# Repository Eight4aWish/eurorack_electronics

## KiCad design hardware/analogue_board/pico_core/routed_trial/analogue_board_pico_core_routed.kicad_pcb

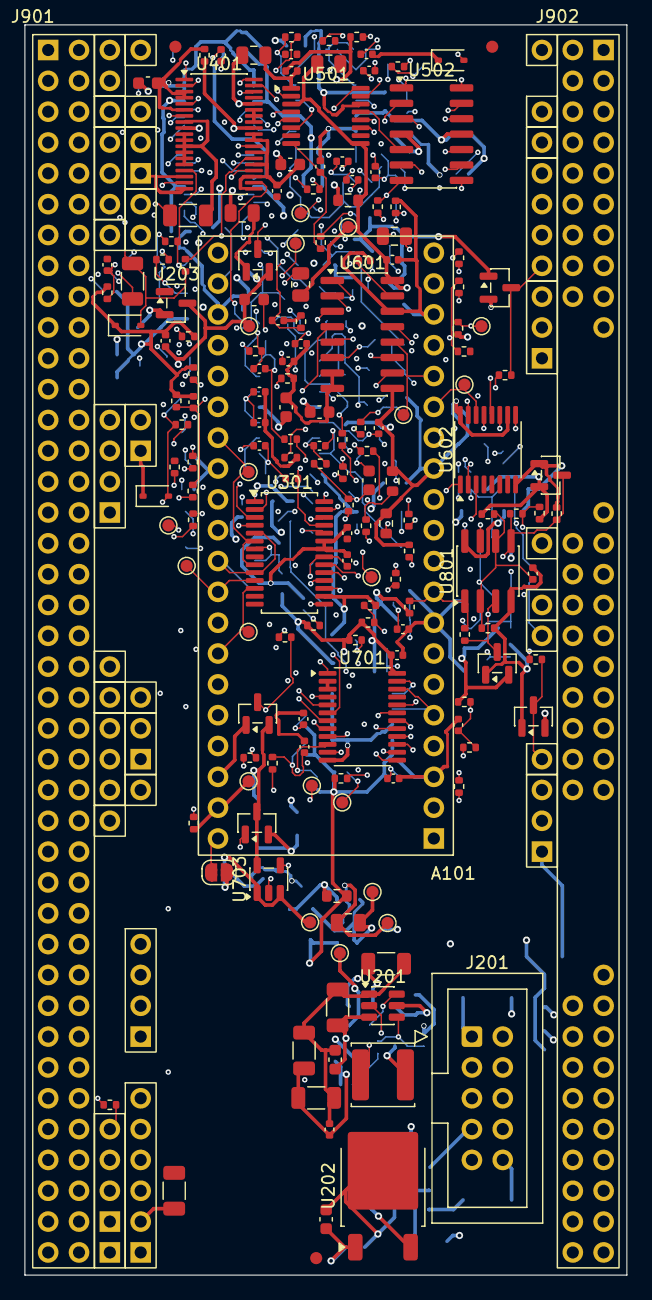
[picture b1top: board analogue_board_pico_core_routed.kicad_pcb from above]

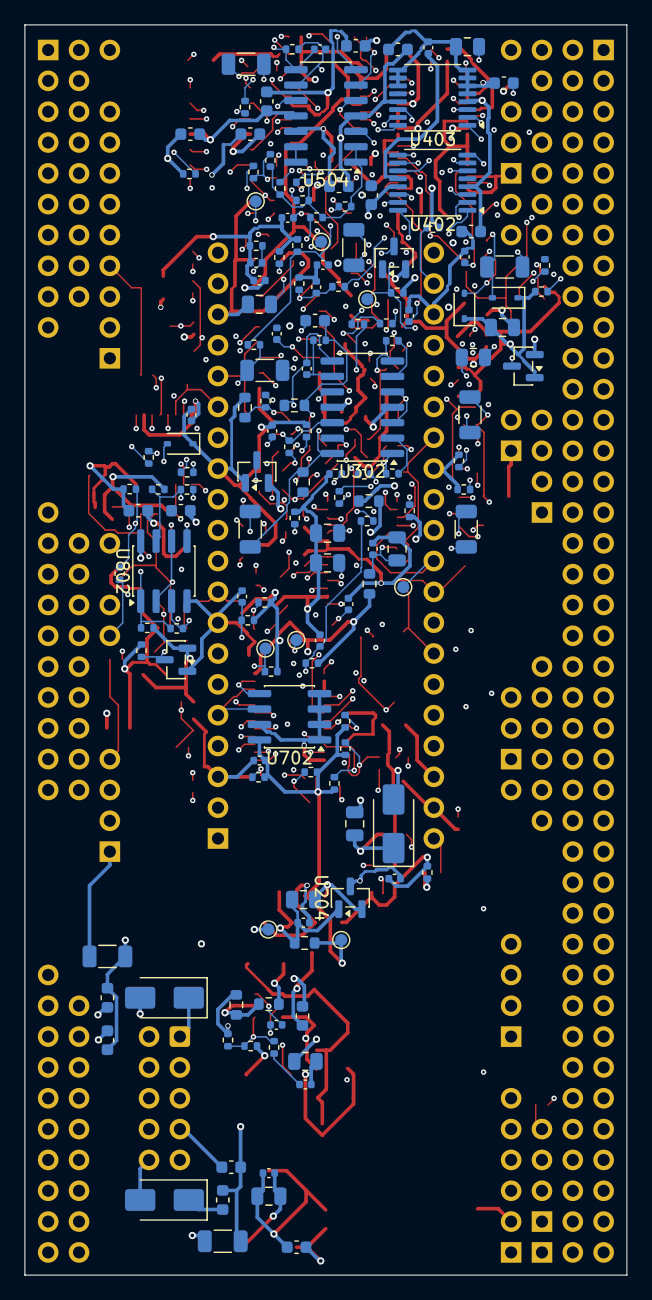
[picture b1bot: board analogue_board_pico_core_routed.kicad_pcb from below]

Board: 6 copper layers, 49.6 x 103.0 mm, 354 parts (152 on the bottom side), 252 nets.

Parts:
A101: Raspberry Pi Pico 2; Pico2_Socket
C201, C203, C205, C206: 10u 50V; C_1206_3216Metric
C202, C204, C207, C215, C319, C320, C415, C416, C418, C419, C511, C512, C513, C514, C801, C802: 100n 50V; C_0603_1608Metric
C208, C212, C217, C302, C304, C306, C309, C312, C405, C417, C420, C502, C602, C604, C605, C606, C607, C608, C609, C610, C611, C701, C702, C703, C704, C705, C710, C711, C712, C803: 100n 16V; C_0402_1005Metric
C209: 470p 50V; C_0402_1005Metric
C210, C211, C407: 22u 25V; C_1206_3216Metric
C213, C216, C219, C221, C222, C301, C303, C305, C403, C404, C408, C501, C603: 10u 25V; C_0805_2012Metric
C214, C401, C402, C406: 1u 50V; C_0603_1608Metric
C218, C220, C503, C601: 1u 25V; C_0402_1005Metric
C307, C310, C313, C314, C316, C317, C505, C506, C507, C508, C509, C510: 100p 50V; C_0402_1005Metric
C308, C311: 1u 50V; C_0805_2012Metric
C315, C318: 1n C0G 50V; C_0603_1608Metric
C409, C410, C411, C412, C413, C414, C504: 1n 50V; C_0402_1005Metric
C706, C707, C708, C709: 10n 50V; C_0402_1005Metric
C713: 47u 10V; C_1206_3216Metric
D201, D202, D203: SS34; D_SMA
D301, D302, D801, D802, D803, D804: BAT54S; SOT-23
D401, D402, D403, D404, D405, D406: PESD15VL1BA; D_SOD-323
D601, D602, D603, D604: BAV99; SOT-23
FB201, FB202, FB203, FB301: BLM18PG121; L_0603_1608Metric
FID901, FID902, FID903: Fiducial; Fiducial_1mm_Mask2mm
J101: Spare GPIO, RUN; WiringHoles_1x04_G4
J201: Eurorack power 2x5 shrouded; IDC-Header_2x05_P2.54mm_Vertical
J303: Codec RST; WiringHoles_1x02_G2
J310, J412, J710, J810: Holes, left top; WiringHoles_1x01
J311, J411, J711, J713, J811: Holes, left bottom; WiringHoles_1x01
J312, J413, J812: Holes, right top; WiringHoles_1x01
J313, J414, J615, J813: Holes, right middle; WiringHoles_1x01
J410, J712: Holes, left top; WiringHoles_1x02
J603: Gate expansion: QH', SRCLK, RCLK, OE; WiringHoles_1x06_G6
J610: Holes, left top; WiringHoles_1x03
J611: Holes, left bottom; WiringHoles_1x03
J612: Holes, left top; WiringHoles_1x02_G2
J613: Holes, left bottom; WiringHoles_1x02_G2
J614: Holes, right top; WiringHoles_1x04
J703: I2C holes for a wired display; WiringHoles_1x04_G4
J704: WS2812 chain holes; WiringHoles_1x05_G4_5
J714: Holes, right top; WiringHoles_1x03_G3
J715: Holes, right middle; WiringHoles_1x03_G3
J901: Edge strip, left; EdgeStrip_40_Left
J902: Edge strip, right; EdgeStrip_40_Right
JP201: ESP32-P4: bridge; SolderJumper-2_P1.3mm_Open_RoundedPad1.0x1.5mm
L201: 15uH; L_Sunlord_SWPA5040S
Q201: AO3401A; SOT-23
R201: 510k; R_0603_1608Metric
R202: 75k; R_0603_1608Metric
R203, R307, R311: 15k; R_0402_1005Metric
R204, R205: 2k; R_0402_1005Metric
R206: 0R; R_0805_2012Metric
R207, R208, R209: 0R; R_0603_1608Metric
R210: 680R; R_0603_1608Metric
R211, R309, R313, R604, R606, R608, R610, R612, R614: 1M; R_0402_1005Metric
R212, R308, R312, R405, R409, R413, R417, R421, R425, R802, R803, R806, R807, R810, R811, R814, R815: 100k; R_0402_1005Metric
R301, R302, R303, R401, R402, R403, R501, R504, R506, R508, R510, R512, R514, R602, R615, R616, R701, R703, R705, R707, R709, R711, R713, R715, R717, R719, R801, R804, R805, R808, R809, R812, R813, R816, R817, R818: 10k; R_0402_1005Metric
R304: 5.1R; R_0603_1608Metric
R305, R310, R314, R317, R318, R324, R325, R404, R408, R412, R416, R420, R424, R603, R605, R607, R609, R611, R613, R617, R618, R619, R620, R702, R704, R706, R708, R710, R712, R714, R716, R718: 1k; R_0402_1005Metric
R306: 220k; R_0603_1608Metric
R315, R316, R322, R323, R502: 12k; R_0402_1005Metric
R319, R320, R326, R327: 30k; R_0603_1608Metric
R321, R328, R406, R410, R414, R418, R422, R426: 1k; R_1206_3216Metric
R407, R411, R415, R419, R423, R427: 4.7k; R_0402_1005Metric
R503: 22k; R_0402_1005Metric
R505, R507, R509, R511, R513, R515: 33k; R_0402_1005Metric
R601: 100R; R_0805_2012Metric
R720, R721: 2.2k; R_0402_1005Metric
R722: 330R; R_0402_1005Metric
TP201: +12V; TestPoint_Pad_D1.0mm
TP202: -12V; TestPoint_Pad_D1.0mm
TP203, TP204: GND; TestPoint_Pad_D1.0mm
TP205: +5VD; TestPoint_Pad_D1.0mm
TP206: +5VA; TestPoint_Pad_D1.0mm
TP207: +3V3A; TestPoint_Pad_D1.0mm
TP208: +3V3D; TestPoint_Pad_D1.0mm
TP209: MOD_5V; TestPoint_Pad_D1.0mm
TP301: MCLK; TestPoint_Pad_D1.0mm
TP302: BCK; TestPoint_Pad_D1.0mm
TP303: LRCK; TestPoint_Pad_D1.0mm
TP304: I2S_DOUT; TestPoint_Pad_D1.0mm
TP305: I2S_DIN; TestPoint_Pad_D1.0mm
TP401: SPIA_SCK; TestPoint_Pad_D1.0mm
TP402: SPIA_MOSI; TestPoint_Pad_D1.0mm
TP403: SPIA_MISO; TestPoint_Pad_D1.0mm
TP404: CS_ADC; TestPoint_Pad_D1.0mm
TP405: CS_DAC; TestPoint_Pad_D1.0mm
TP601: SPIB_SCK; TestPoint_Pad_D1.0mm
TP602: SPIB_MOSI; TestPoint_Pad_D1.0mm
TP603: SPIB_MISO; TestPoint_Pad_D1.0mm
TP604: CS_595; TestPoint_Pad_D1.0mm
TP605: CS_POT; TestPoint_Pad_D1.0mm
TP701: SDA; TestPoint_Pad_D1.0mm
TP702: SCL; TestPoint_Pad_D1.0mm
TP703: EXP_INT; TestPoint_Pad_D1.0mm
U201: TPS54308DDCR; SOT-23-6
U202: L78M05ABDT-TR; TO-252-2_PasteShapes
U203, U204: XC6206P332MR-G; SOT-23
U301: PCM3060PWR; TSSOP-28_4.4x9.7mm_P0.65mm
U302, U502, U504: TL074HIDR; SOIC-14_3.9x8.7mm_P1.27mm
U401: ADS8688IDBTR; TSSOP-38_4.4x9.7mm_P0.5mm
U402, U403: DG412DQ-T1-E3; TSSOP-16_4.4x5mm_P0.65mm
U501: DAC8568IAPWR; TSSOP-16_4.4x5mm_P0.65mm
U601: MCP3208-CI/SL; SOIC-16_3.9x9.9mm_P1.27mm
U602: 74HCT595PW; TSSOP-16_4.4x5mm_P0.65mm
U701: TCA9555PWR; TSSOP-24_4.4x7.8mm_P0.65mm
U702: M24C64-RMN6TP; SOIC-8_3.9x4.9mm_P1.27mm
U703: SN74AHCT1G125DBVR; SOT-23-5
U801, U802: LM393DR2G; SOIC-8_3.9x4.9mm_P1.27mm

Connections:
+3V3A: C501.1, C502.1, C601.1, C602.1, R208.2, R601.1, TP207.1, U501.3, U501.9, U601.16
+3V3D: C404.1, C405.1, C701.1, C711.1, D801.2, D802.2, D803.2, D804.2, J703.3, R209.2, R210.1, R304.1, R305.1, R401.1, R402.1, R501.1, R602.1, R615.1, R616.1, R701.1, R703.1, R705.1, R707.1, R709.1, R711.1, R713.1, R715.1, R717.1, R719.1, R720.1, R721.1, R804.1, R808.1, R812.1, R816.1, R817.1, TP208.1, U401.34, U701.24, U702.8
+5VA: C218.1, C401.1, C402.1, C403.1, D301.2, D302.2, FB301.1, R207.2, R403.1, TP206.1, U203.3, U401.9, U401.30
+5VD: C213.1, C220.1, C417.1, C420.1, C611.1, C712.1, C713.1, D203.2, D601.2, D602.2, D603.2, D604.2, J603.5, J704.2, J704.3, Q201.3, R206.2, TP205.1, U204.3, U402.12, U403.12, U602.10, U602.16, U703.5
+12V: C201.1, C202.1, C214.1, C215.1, C319.1, C415.1, C418.1, C511.1, C513.1, C801.1, C802.1, FB201.2, FB203.1, TP201.1, U202.1, U302.4, U402.13, U403.13, U502.4, U504.4, U801.8, U802.8
-12V: C203.1, C204.1, C320.1, C416.1, C419.1, C512.1, C514.1, FB202.2, TP202.1, U302.11, U402.4, U403.4, U502.11, U504.11
/CV DAC/DAC1: U501.4, U502.3
/CV DAC/DAC2: U501.13, U502.5
/CV DAC/DAC3: U501.5, U502.10
/CV DAC/DAC4: U501.12, U502.12
/CV DAC/DAC5: U501.6, U504.5
/CV DAC/DAC6: U501.11, U504.10
/CV DAC/DAC_VREF: C503.1, R502.1, U501.8
/CV DAC/OFFSET_REF: R504.1, R506.1, R508.1, R510.1, R512.1, R514.1, U504.1, U504.2
/CV DAC/OFFS_DIV: C504.1, R502.2, R503.1, U504.3
/CV jacks & ADC/ADC_IN1: C409.1, R404.2, R405.1, U401.16
/CV jacks & ADC/ADC_IN2: C410.1, R408.2, R409.1, U401.18
/CV jacks & ADC/ADC_IN3: C411.1, R412.2, R413.1, U401.21
/CV jacks & ADC/ADC_IN4: C412.1, R416.2, R417.1, U401.23
/CV jacks & ADC/ADC_IN5: C413.1, R420.2, R421.1, U401.25
/CV jacks & ADC/ADC_IN6: C414.1, R424.2, R425.1, U401.27
/CV jacks & ADC/ADC_RST: R401.2, U401.2
/CV jacks & ADC/CV1: D401.2, J410.1, R404.1, R406.2
/CV jacks & ADC/CV2: D402.2, J412.1, R408.1, R410.2
/CV jacks & ADC/CV3: D403.2, J411.1, R412.1, R414.2
/CV jacks & ADC/CV4: D404.2, J413.1, R416.1, R418.2
/CV jacks & ADC/CV5: D405.2, J410.2, R420.1, R422.2
/CV jacks & ADC/CV6: D406.2, J414.1, R424.1, R426.2
/CV jacks & ADC/REFCAP: C406.1, C407.1, U401.7
/CV jacks & ADC/REFIO: C408.1, U401.5
/Codec & audio/AIN1: C308.1, J310.1, R309.1
/Codec & audio/AIN2: C311.1, J312.1, R313.1
/Codec & audio/AOUT1: J311.1, R321.2
/Codec & audio/AOUT2: J313.1, R328.2
/Codec & audio/CODEC_DEMP: R302.1, U301.2
/Codec & audio/CODEC_FMT: R301.1, U301.1
/Codec & audio/CODEC_IFMD: R303.1, U301.27
/Codec & audio/CODEC_MODE: R306.1, U301.28
/Codec & audio/CODEC_RST: J303.1, R305.2, U301.15
/Codec & audio/CODEC_VCC: C301.1, C302.1, FB301.2, U301.24
/Codec & audio/CODEC_VDD: C303.1, C304.1, R304.2, U301.7
/Codec & audio/VCOM: C305.1, C306.1, C309.1, C312.1, U301.21, U302.3, U302.5
/Codec & audio/VINL: D301.3, R310.2, U301.25
/Codec & audio/VINR: D302.3, R314.2, U301.26
/Codec & audio/VOUTL_N: R315.1, U301.19
/Codec & audio/VOUTL_P: R316.1, U301.20
/Codec & audio/VOUTR_N: R322.1, U301.17
/Codec & audio/VOUTR_P: R323.1, U301.18
/Edge strips/DECK_L1: J901.1, J901.41
/Edge strips/DECK_L2: J901.2, J901.42
/Edge strips/DECK_L3: J901.3, J901.43
/Edge strips/DECK_L4: J901.4, J901.44
/Edge strips/DECK_L5: J901.5, J901.45
/Edge strips/DECK_L6: J901.6, J901.46
/Edge strips/DECK_L7: J901.7, J901.47
/Edge strips/DECK_L8: J901.8, J901.48
/Edge strips/DECK_L9: J901.9, J901.49
/Edge strips/DECK_L10: J901.10, J901.50
/Edge strips/DECK_L11: J901.11, J901.51
/Edge strips/DECK_L12: J901.12, J901.52
/Edge strips/DECK_L13: J901.13, J901.53
/Edge strips/DECK_L14: J901.14, J901.54
/Edge strips/DECK_L15: J901.15, J901.55
/Edge strips/DECK_L16: J901.16, J901.56
/Edge strips/DECK_L17: J901.17, J901.57
/Edge strips/DECK_L18: J901.18, J901.58
/Edge strips/DECK_L19: J901.19, J901.59
/Edge strips/DECK_L20: J901.20, J901.60
/Edge strips/DECK_L21: J901.21, J901.61
/Edge strips/DECK_L22: J901.22, J901.62
/Edge strips/DECK_L23: J901.23, J901.63
/Edge strips/DECK_L24: J901.24, J901.64
/Edge strips/DECK_L25: J901.25, J901.65
/Edge strips/DECK_L26: J901.26, J901.66
/Edge strips/DECK_L27: J901.27, J901.67
/Edge strips/DECK_L28: J901.28, J901.68
/Edge strips/DECK_L29: J901.29, J901.69
/Edge strips/DECK_L30: J901.30, J901.70
/Edge strips/DECK_L31: J901.31, J901.71
/Edge strips/DECK_L32: J901.32, J901.72
/Edge strips/DECK_L33: J901.33, J901.73
/Edge strips/DECK_L34: J901.34, J901.74
/Edge strips/DECK_L35: J901.35, J901.75
/Edge strips/DECK_L36: J901.36, J901.76
/Edge strips/DECK_L37: J901.37, J901.77
/Edge strips/DECK_L38: J901.38, J901.78
/Edge strips/DECK_L39: J901.39, J901.79
/Edge strips/DECK_L40: J901.40, J901.80
/Edge strips/DECK_R1: J902.1, J902.41
/Edge strips/DECK_R2: J902.2, J902.42
/Edge strips/DECK_R3: J902.3, J902.43
/Edge strips/DECK_R4: J902.4, J902.44
/Edge strips/DECK_R5: J902.5, J902.45
/Edge strips/DECK_R6: J902.6, J902.46
/Edge strips/DECK_R7: J902.7, J902.47
/Edge strips/DECK_R8: J902.8, J902.48
/Edge strips/DECK_R9: J902.9, J902.49
/Edge strips/DECK_R17: J902.17, J902.57
/Edge strips/DECK_R18: J902.18, J902.58
/Edge strips/DECK_R19: J902.19, J902.59
/Edge strips/DECK_R20: J902.20, J902.60
/Edge strips/DECK_R21: J902.21, J902.61
/Edge strips/DECK_R22: J902.22, J902.62
/Edge strips/DECK_R23: J902.23, J902.63
/Edge strips/DECK_R24: J902.24, J902.64
/Edge strips/DECK_R25: J902.25, J902.65
/Edge strips/DECK_R32: J902.32, J902.72
/Edge strips/DECK_R33: J902.33, J902.73
/Edge strips/DECK_R34: J902.34, J902.74
/Edge strips/DECK_R35: J902.35, J902.75
/Edge strips/DECK_R36: J902.36, J902.76
/Edge strips/DECK_R37: J902.37, J902.77
/Edge strips/DECK_R38: J902.38, J902.78
/Edge strips/DECK_R39: J902.39, J902.79
/Edge strips/DECK_R40: J902.40, J902.80
/Expander, I2C & LEDs/BTN1: C702.1, R702.2, R703.2, U701.13
/Expander, I2C & LEDs/BTN2: C703.1, R704.2, R705.2, U701.14
/Expander, I2C & LEDs/BTN3: C704.1, R706.2, R707.2, U701.15
/Expander, I2C & LEDs/BTN4: C705.1, R708.2, R709.2, U701.16
/Expander, I2C & LEDs/BTN5: C706.1, R710.2, R711.2, U701.17
/Expander, I2C & LEDs/BTN6: C707.1, R712.2, R713.2, U701.18
/Expander, I2C & LEDs/BTN7: C708.1, R714.2, R715.2, U701.19
/Expander, I2C & LEDs/BTN8: C709.1, R716.2, R717.2, U701.20
/Expander, I2C & LEDs/BTN9: C710.1, R718.2, R719.2, U701.11
/Expander, I2C & LEDs/LED_BUF: R722.1, U703.4
/Expander, I2C & LEDs/LED_DIN: J704.1, R722.2
/Expander, I2C & LEDs/SW1: J712.1, R702.1
/Expander, I2C & LEDs/SW2: J710.1, R704.1
/Expander, I2C & LEDs/SW3: J712.2, R706.1
/Expander, I2C & LEDs/SW4: J713.1, R708.1
/Expander, I2C & LEDs/SW5: J711.1, R710.1
/Expander, I2C & LEDs/SW6: J714.1, R712.1
/Expander, I2C & LEDs/SW7: J714.2, R714.1
/Expander, I2C & LEDs/SW8: J715.1, R716.1
/Expander, I2C & LEDs/SW9: J715.2, R718.1
/Gate ins/GATE_TH: C803.1, R817.2, R818.1, U801.2, U801.6, U802.2, U802.6
/Gate ins/GIN1: J810.1, R801.1
/Gate ins/GIN2: J811.1, R805.1
/Gate ins/GIN3: J812.1, R809.1
/Gate ins/GIN4: J813.1, R813.1
/Pots & gate outs/GATE_SER_OUT: J603.1, U602.9
/Pots & gate outs/GOUT1: D601.3, J610.3, R617.2
/Pots & gate outs/GOUT2: D602.3, J611.3, R618.2
/Pots & gate outs/GOUT3: D603.3, J614.4, R619.2
/Pots & gate outs/GOUT4: D604.3, J615.1, R620.2
/Pots & gate outs/GQ1: R617.1, U602.15
/Pots & gate outs/GQ2: R618.1, U602.1
/Pots & gate outs/GQ3: R619.1, U602.2
/Pots & gate outs/GQ4: R620.1, U602.3
/Pots & gate outs/POT1: J610.1, R603.1
/Pots & gate outs/POT2: J612.1, R605.1
/Pots & gate outs/POT3: J611.1, R607.1
/Pots & gate outs/POT4: J613.1, R609.1
/Pots & gate outs/POT5: J614.1, R611.1
/Pots & gate outs/POT6: J614.2, R613.1
/Pots & gate outs/POT_IN1: C605.1, R603.2, R604.1, U601.1
/Pots & gate outs/POT_IN2: C606.1, R605.2, R606.1, U601.2
/Pots & gate outs/POT_IN3: C607.1, R607.2, R608.1, U601.3
/Pots & gate outs/POT_IN4: C608.1, R609.2, R610.1, U601.4
/Pots & gate outs/POT_IN5: C609.1, R611.2, R612.1, U601.5
/Pots & gate outs/POT_IN6: C610.1, R613.2, R614.1, U601.6
/Pots & gate outs/POT_REF: C603.1, C604.1, J610.2, J611.2, J614.3, R601.2, U601.15
/Power/3V3A_REG: C219.1, R208.1, U203.2
/Power/3V3D_REG: C221.1, R209.1, U204.2
/Power/5VA_REG: C216.1, C217.1, R207.1, U202.3
/Power/5V_BUCK: C209.1, C210.1, C211.1, C212.1, L201.2, R203.1, R206.1
/Power/+12V_IN: D201.2, J201.9, J201.10
/Power/+12V_P: D201.1, FB201.1
/Power/-12V_IN: D202.1, J201.1, J201.2
/Power/-12V_P: D202.2, FB202.1
/Power/BUCK_EN: R201.2, R202.1, U201.5
/Power/BUCK_VIN: C205.1, C206.1, C207.1, FB203.2, R201.1, U201.3
/Power/FET_EN: JP201.2, R212.1
/RUN: A101.30, J101.3
BCK: A101.31, TP302.1, U301.5, U301.10
CS_595: A101.17, J603.3, R616.2, TP604.1, U602.12
CS_ADC: A101.22, R402.2, TP404.1, U401.38
CS_DAC: A101.26, R501.2, TP405.1, U501.2
CS_POT: A101.19, R602.2, TP605.1, U601.10
CVDRV1: C505.2, R505.2, U402.3, U502.1
CVDRV2: C506.2, R507.2, U402.14, U502.7
CVDRV3: C507.2, R509.2, U402.11, U502.8
CVDRV4: C508.2, R511.2, U402.7, U502.14
CVDRV5: C509.2, R513.2, U403.3, U504.7
CVDRV6: C510.2, R515.2, U403.14, U504.8
EXP_INT: A101.6, R701.2, TP703.1, U701.1
GATE_IN1: A101.9, R803.2, R804.2, U801.1
GATE_IN2: A101.10, R807.2, R808.2, U801.7
GATE_IN3: A101.11, R811.2, R812.2, U802.1
GATE_IN4: A101.12, R815.2, R816.2, U802.7
GATE_OE_N: J603.4, R615.2, U602.13, U701.10
GND: A101.3, A101.8, A101.13, A101.18, A101.23, A101.28, A101.33, A101.38, C201.2, C202.2, C203.2, C204.2, C205.2, C206.2, C207.2, C210.2, C211.2, C212.2, C213.2, C214.2, C215.2, C216.2, C217.2, C218.2, C219.2, C220.2, C221.2, C222.2, C301.2, C302.2, C303.2, C304.2, C305.2, C306.2, C309.2, C312.2, C314.2, C317.2, C319.2, C320.2, C401.2, C402.2, C403.2, C404.2, C405.2, C406.2, C407.2, C408.2, C409.2, C410.2, C411.2, C412.2, C413.2, C414.2, C415.2, C416.2, C417.2, C418.2, C419.2, C420.2, C501.2, C502.2, C503.2, C504.2, C511.2, C512.2, C513.2, C514.2, C601.2, C602.2, C603.2, C604.2, C605.2, C606.2, C607.2, C608.2, C609.2, C610.2, C611.2, C701.2, C702.2, C703.2, C704.2, C705.2, C706.2, C707.2, C708.2, C709.2, C710.2, C711.2, C712.2, C713.2, C801.2, C802.2, C803.2, D301.1, D302.1, D401.1, D402.1, D403.1, D404.1, D405.1, D406.1, D601.1, D602.1, D603.1, D604.1, D801.1, D802.1, D803.1, D804.1, J101.4, J201.3, J201.4, J201.5, J201.6, J201.7, J201.8, J303.2, J603.6, J612.2, J613.2, J703.4, J704.4, J704.5, J714.3, J715.3, R202.2, R204.2, R210.2, R212.2, R301.2, R302.2, R303.2, R306.2, R309.2, R313.2, R320.2, R327.2, R403.2, R405.2, R407.2, R409.2, R411.2, R413.2, R415.2, R417.2, R419.2, R421.2, R423.2, R425.2, R427.2, R503.2, R604.2, R606.2, R608.2, R610.2, R612.2, R614.2, R802.2, R806.2, R810.2, R814.2, R818.2, TP203.1, TP204.1, U201.1, U202.2, U203.1, U204.1, U301.8, U301.16, U301.22, U301.23, U401.3, U401.4, U401.6, U401.8, U401.10, U401.11, U401.12, U401.13, U401.14, U401.15, U401.17, U401.19, U401.20, U401.22, U401.24, U401.26, U401.28, U401.29, U401.31, U401.32, U401.33, U402.5, U403.5, U403.6, U403.7, U403.8, U403.9, U403.10, U403.11, U501.1, U501.14, U504.12, U601.7, U601.8, U601.9, U601.14, U602.8, U701.2, U701.3, U701.12, U701.21, U702.1, U702.2, U702.3, U702.4, U702.7, U703.1, U703.3, U801.4, U802.4
I2S_DIN: A101.29, TP305.1, U301.3
I2S_DOUT: A101.34, TP304.1, U301.12
LED_DATA: A101.7, U703.2
LRCK: A101.32, TP303.1, U301.4, U301.11
MCLK: A101.27, TP301.1, U301.6, U301.9
MOD_5V: A101.39, C222.1, D203.1, Q201.2, R211.1, TP209.1
unnamed: C209.2, R205.1
unnamed: C307.2, R307.2, R310.1, U302.1
unnamed: C308.2, R308.1
unnamed: C310.2, R311.2, R314.1, U302.7
unnamed: C311.2, R312.1
unnamed: C313.2, R319.2, R321.1, U302.8
unnamed: C315.1, R315.2, R317.1, R319.1
unnamed: C315.2, R316.2, R318.1, R320.1
unnamed: C316.2, R326.2, R328.1, U302.14
unnamed: C318.1, R322.2, R324.1, R326.1
unnamed: C318.2, R323.2, R325.1, R327.1
unnamed: D801.3, R801.2, R802.1, R803.1, U801.3
unnamed: D802.3, R805.2, R806.1, R807.1, U801.5
unnamed: D803.3, R809.2, R810.1, R811.1, U802.3
unnamed: D804.3, R813.2, R814.1, R815.1, U802.5
unnamed: R406.1, U402.2
unnamed: R410.1, U402.15
unnamed: R414.1, U402.10
unnamed: R418.1, U402.6
unnamed: R422.1, U403.2
unnamed: R426.1, U403.15
unnamed: C208.1, U201.6
unnamed: R203.2, R204.1, R205.2, U201.4
unnamed: C208.2, L201.1, U201.2
unnamed: C307.1, R307.1, R308.2, U302.2
unnamed: C310.1, R311.1, R312.2, U302.6
unnamed: C314.1, R318.2, U302.10
unnamed: C313.1, R317.2, U302.9
unnamed: C317.1, R325.2, U302.12
unnamed: C316.1, R324.2, U302.13
unnamed: C505.1, R504.2, R505.1, U502.2
unnamed: C506.1, R506.2, R507.1, U502.6
unnamed: C507.1, R508.2, R509.1, U502.9
unnamed: C508.1, R510.2, R511.1, U502.13
unnamed: C509.1, R512.2, R513.1, U504.6
unnamed: C510.1, R514.2, R515.1, U504.9
unnamed: U504.13, U504.14
PICO_VBUS: A101.40, JP201.1, Q201.1, R211.2
SCL: A101.5, J703.2, R721.2, TP702.1, U701.22, U702.6
SDA: A101.4, J703.1, R720.2, TP701.1, U701.23, U702.5
SPARE1: A101.1, J101.1
SPARE2: A101.2, J101.2
SPIA_MISO: A101.21, TP403.1, U401.36
SPIA_MOSI: A101.25, TP402.1, U401.1, U501.15
SPIA_SCK: A101.24, TP401.1, U401.37, U501.16
SPIB_MISO: A101.16, TP603.1, U601.12
SPIB_MOSI: A101.15, TP602.1, U601.11, U602.14
SPIB_SCK: A101.14, J603.2, TP601.1, U601.13, U602.11
SW_EN1: R407.1, U402.1, U701.4
SW_EN2: R411.1, U402.16, U701.5
SW_EN3: R415.1, U402.9, U701.6
SW_EN4: R419.1, U402.8, U701.7
SW_EN5: R423.1, U403.1, U701.8
SW_EN6: R427.1, U403.16, U701.9

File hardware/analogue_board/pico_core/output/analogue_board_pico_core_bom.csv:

"Refs","Value","Footprint","LCSC","MPN","JLC","Qty"
"A101","Raspberry Pi Pico 2","analogue_board:Pico2_Socket","","SC1631 on 2x20 female headers","hand-soldered","1"
"C201,C203,C205,C206","10u 50V","Capacitor_SMD:C_1206_3216Metric","C13585","","Basic","4"
"C202,C204,C207,C215,C319,C320,C415,C416,C418,C419,C511-C514,C801,C802","100n 50V","Capacitor_SMD:C_0603_1608Metric","C14663","","Basic","16"
"C208,C212,C217,C302,C304,C306,C309,C312,C405,C417,C420,C502,C602,C604-C611,C701-C705,C710-C712,C803","100n 16V","Capacitor_SMD:C_0402_1005Metric","C1525","","Basic","30"
"C210,C211,C407","22u 25V","Capacitor_SMD:C_1206_3216Metric","C12891","","Basic","3"
"C213,C216,C219,C221,C222,C301,C303,C305,C403,C404,C408,C501,C603","10u 25V","Capacitor_SMD:C_0805_2012Metric","C15850","","Basic","13"
"C214,C401,C402,C406","1u 50V","Capacitor_SMD:C_0603_1608Metric","C15849","","Basic","4"
"C218,C220,C503,C601","1u 25V","Capacitor_SMD:C_0402_1005Metric","C52923","","Basic","4"
"C307,C310,C313,C314,C316,C317,C505-C510","100p 50V","Capacitor_SMD:C_0402_1005Metric","C1546","","Basic","12"
"C308,C311","1u 50V","Capacitor_SMD:C_0805_2012Metric","C28323","","Basic","2"
"C315,C318","1n C0G 50V","Capacitor_SMD:C_0603_1608Metric","C106246","","Extended","2"
"C409-C414,C504","1n 50V","Capacitor_SMD:C_0402_1005Metric","C1523","","Basic","7"
"C706-C709","10n 50V","Capacitor_SMD:C_0402_1005Metric","C15195","","Basic","4"
"C713","47u 10V","Capacitor_SMD:C_1206_3216Metric","C96123","","Basic","1"
"D201-D203","SS34","Diode_SMD:D_SMA","C8678","SS34","Basic","3"
"D301,D302,D801-D804","BAT54S","Package_TO_SOT_SMD:SOT-23","C408389","BAT54S","Extended","6"
"D401-D406","PESD15VL1BA","Diode_SMD:D_SOD-323","C85378","PESD15VL1BA,115","Extended","6"
"D601-D604","BAV99","Package_TO_SOT_SMD:SOT-23","C2500","BAV99,215","Basic","4"
"FB201-FB203,FB301","BLM18PG121","Inductor_SMD:L_0603_1608Metric","C14709","BLM18PG121SN1D","Basic","4"
"J201","Eurorack power 2x5 shrouded","Connector_IDC:IDC-Header_2x05_P2.54mm_Vertical","","2x5 2.54 mm shrouded box header","hand-soldered","1"
"L201","15uH","Inductor_SMD:L_Sunlord_SWPA5040S","C44888","SWPA5040S150MT","Extended","1"
"Q201","AO3401A","Package_TO_SOT_SMD:SOT-23","C15127","AO3401A","Basic","1"
"R201","510k","Resistor_SMD:R_0603_1608Metric","C23192","","Basic","1"
"R202","75k","Resistor_SMD:R_0603_1608Metric","C23242","","Basic","1"
"R203,R307,R311","15k","Resistor_SMD:R_0402_1005Metric","C25756","","Basic","3"
"R204","2k","Resistor_SMD:R_0402_1005Metric","C4109","","Basic","1"
"R206","0R","Resistor_SMD:R_0805_2012Metric","C17477","","Basic","1"
"R207-R209","0R","Resistor_SMD:R_0603_1608Metric","C21189","","Basic","3"
"R210","680R","Resistor_SMD:R_0603_1608Metric","C23228","","Basic","1"
"R211,R309,R313,R604,R606,R608,R610,R612,R614","1M","Resistor_SMD:R_0402_1005Metric","C26083","","Basic","9"
"R212,R308,R312,R405,R409,R413,R417,R421,R425,R802,R803,R806,R807,R810,R811,R814,R815","100k","Resistor_SMD:R_0402_1005Metric","C25741","","Basic","17"
"R301-R303,R401-R403,R501,R504,R506,R508,R510,R512,R514,R602,R615,R616,R701,R703,R705,R707,R709,R711,R713,R715,R717,R719,R801,R804,R805,R808,R809,R812,R813,R816-R818","10k","Resistor_SMD:R_0402_1005Metric","C25744","","Basic","36"
"R304","5.1R","Resistor_SMD:R_0603_1608Metric","C25197","","Basic","1"
"R305,R310,R314,R317,R318,R324,R325,R404,R408,R412,R416,R420,R424,R603,R605,R607,R609,R611,R613,R617-R620,R702,R704,R706,R708,R710,R712,R714,R716,R718","1k","Resistor_SMD:R_0402_1005Metric","C11702","","Basic","32"
"R306","220k","Resistor_SMD:R_0603_1608Metric","C22961","","Basic","1"
"R315,R316,R322,R323,R502","12k","Resistor_SMD:R_0402_1005Metric","C25752","","Basic","5"
"R319,R320,R326,R327","30k","Resistor_SMD:R_0603_1608Metric","C22984","","Basic","4"
"R321,R328,R406,R410,R414,R418,R422,R426","1k","Resistor_SMD:R_1206_3216Metric","C4410","","Basic","8"
"R407,R411,R415,R419,R423,R427","4.7k","Resistor_SMD:R_0402_1005Metric","C25900","","Basic","6"
"R503","22k","Resistor_SMD:R_0402_1005Metric","C25768","","Basic","1"
"R505,R507,R509,R511,R513,R515","33k","Resistor_SMD:R_0402_1005Metric","C25779","","Basic","6"
"R601","100R","Resistor_SMD:R_0805_2012Metric","C17408","","Basic","1"
"R720,R721","2.2k","Resistor_SMD:R_0402_1005Metric","C25879","","Basic","2"
"R722","330R","Resistor_SMD:R_0402_1005Metric","C25104","","Basic","1"
"U201","TPS54308DDCR","Package_TO_SOT_SMD:SOT-23-6","C168839","TPS54308DDCR","Extended","1"
"U202","L78M05ABDT-TR","analogue_board:TO-252-2_PasteShapes","C58069","L78M05ABDT-TR","Basic","1"
"U203,U204","XC6206P332MR-G","Package_TO_SOT_SMD:SOT-23","C5446","XC6206P332MR-G","Basic","2"
"U301","PCM3060PWR","Package_SO:TSSOP-28_4.4x9.7mm_P0.65mm","C2651841","PCM3060PWR","Extended","1"
"U302,U502,U504","TL074HIDR","Package_SO:SOIC-14_3.9x8.7mm_P1.27mm","C2878713","TL074HIDR","Extended","3"
"U401","ADS8688IDBTR","Package_SO:TSSOP-38_4.4x9.7mm_P0.5mm","C527390","ADS8688IDBTR","Extended","1"
"U402,U403","DG412DQ-T1-E3","Package_SO:TSSOP-16_4.4x5mm_P0.65mm","C2651920","DG412DQ-T1-E3","Extended","2"
"U501","DAC8568IAPWR","Package_SO:TSSOP-16_4.4x5mm_P0.65mm","C486051","DAC8568IAPWR","Extended","1"
"U601","MCP3208-CI/SL","Package_SO:SOIC-16_3.9x9.9mm_P1.27mm","C16939","MCP3208-CI/SL","Extended","1"
"U602","74HCT595PW","Package_SO:TSSOP-16_4.4x5mm_P0.65mm","C99710","74HCT595PW,118","Extended","1"
"U701","TCA9555PWR","Package_SO:TSSOP-24_4.4x7.8mm_P0.65mm","C465732","TCA9555PWR","Extended","1"
"U702","M24C64-RMN6TP","Package_SO:SOIC-8_3.9x4.9mm_P1.27mm","C79988","M24C64-RMN6TP","Extended (Preferred)","1"
"U703","SN74AHCT1G125DBVR","Package_TO_SOT_SMD:SOT-23-5","C7484","SN74AHCT1G125DBVR","Extended","1"
"U801,U802","LM393DR2G","Package_SO:SOIC-8_3.9x4.9mm_P1.27mm","C7955","LM393DR2G","Basic","2"
